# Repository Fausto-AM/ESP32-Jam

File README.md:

# ESP32-JAM

A high-performance 2.4 GHz signal jammer built on the **ESP32-WROOM** platform. It utilizes two independent **nRF24L01+PA+LNA** modules to sweep the 2.4 GHz spectrum in parallel, flooding the band with noise at maximum speed and power.

---

> [!WARNING]
> **DO NOT cross the USBs:** The ESP32 is powered directly via its `3V3` pin, bypassing its onboard regulator. **Never** connect a USB cable to the ESP32 dev board for programming while the device is powered by the battery or charging via the TP4056. It will cause a voltage conflict and permanently damage the ESP32 or the LDO. Turn the slide switch OFF before flashing.

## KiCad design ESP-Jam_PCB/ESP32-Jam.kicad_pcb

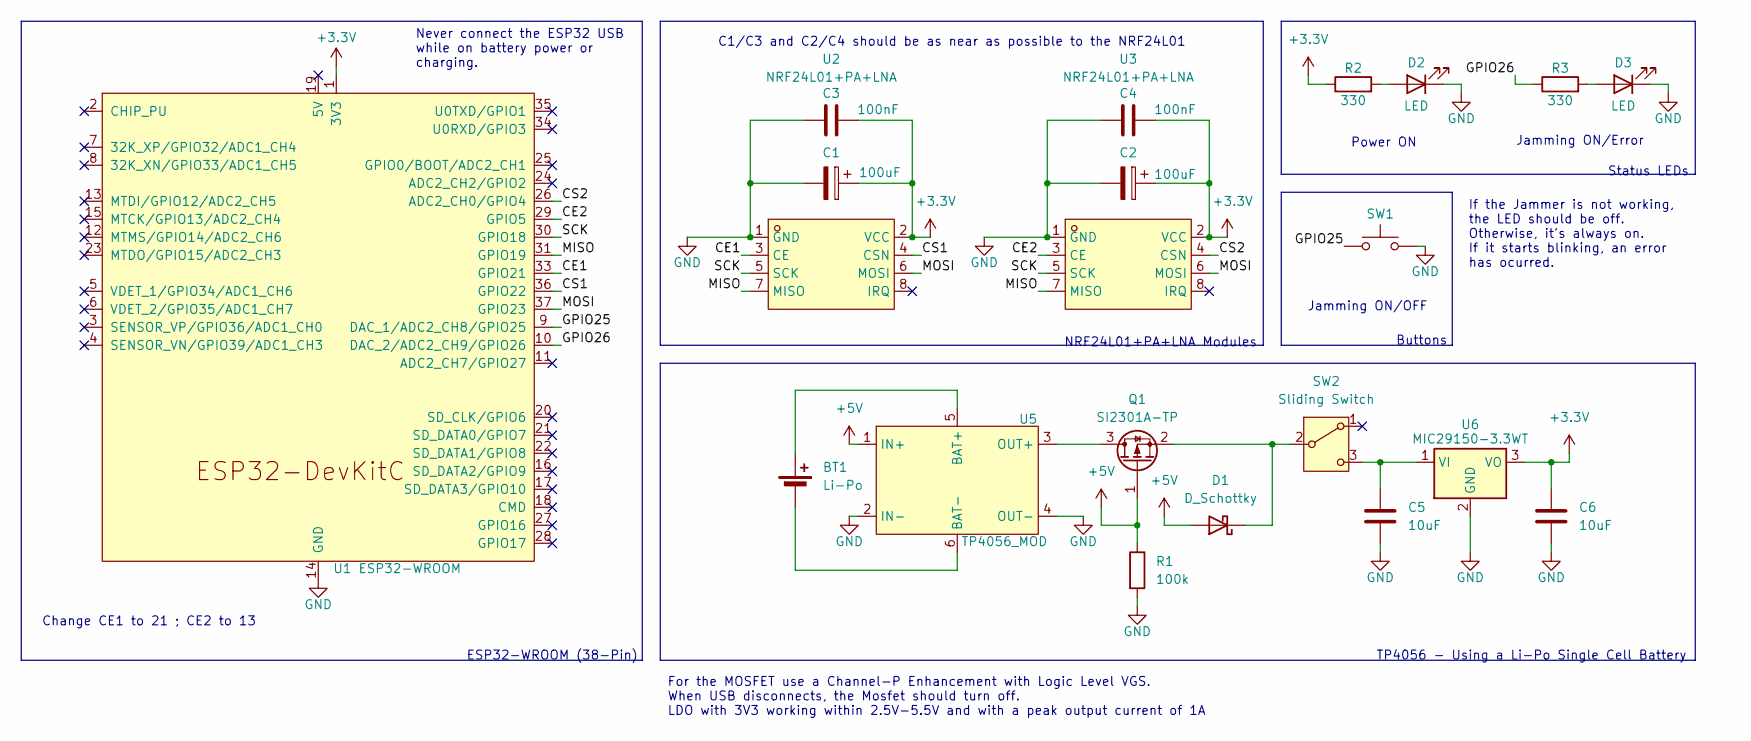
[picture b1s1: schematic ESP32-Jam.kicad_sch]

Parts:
BT1: Li-Po; JST_PH_B2B-PH-K_1x02_P2.00mm_Vertical
C1, C2: 100uF; CP_Radial_D5.0mm_P2.50mm
C3, C4: 100nF; C_Disc_D4.3mm_W1.9mm_P5.00mm
C5, C6: 10uF; C_Disc_D4.3mm_W1.9mm_P5.00mm
D1: D_Schottky; D_DO-35_SOD27_P10.16mm_Horizontal
D2, D3: LED; LED_D1.8mm_W3.3mm_H2.4mm
Q1: SI2301A-TP; SOT-23_Handsoldering
R1: 100k; R_Axial_DIN0204_L3.6mm_D1.6mm_P7.62mm_Horizontal
R2, R3: 330; R_Axial_DIN0204_L3.6mm_D1.6mm_P7.62mm_Horizontal
SW1: SW_Push; SW_TH_Tactile_Omron_B3F-102x
SW2: Sliding Switch; SW_Slide-03_Wuerth-WS-SLTV_10x2.5x6.4_P2.54mm
U1: ESP32-WROOM; ESP32-DevKitC
U2, U3: NRF24L01+PA+LNA; COMM-TH_L41.0-W15.5-P2.54_NRF24L01; MPN nRF24L01+PA+LNA; LCSC Part C9900187674
U5: TP4056_MOD; TP4056-Module
U6: MIC29150-3.3WT; TO-220-3_Horizontal_TabDown

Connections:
+3.3V: C1.1, C2.1, C3.2, C4.2, C6.1, R2.1, U1.1 (3V3), U2.2 (VCC), U3.2 (VCC), U6.3 (VO)
+5V: D1.2 (A), Q1.1 (G), R1.1, U5.1 (IN+)
/CE1: U1.33 (GPIO21), U2.3 (CE)
/CE2: U1.29 (GPIO5), U3.3 (CE)
/CS1: U1.36 (GPIO22), U2.4 (CSN)
/CS2: U1.26 (ADC2_CH0/GPIO4), U3.4 (CSN)
/GPIO25: SW1.1, U1.9 (DAC_1/ADC2_CH8/GPIO25)
/GPIO26: R3.1, U1.10 (DAC_2/ADC2_CH9/GPIO26)
/MISO: U1.31 (GPIO19), U2.7 (MISO), U3.7 (MISO)
/MOSI: U1.37 (GPIO23), U2.6 (MOSI), U3.6 (MOSI)
/SCK: U1.30 (GPIO18), U2.5 (SCK), U3.5 (SCK)
GND: C1.2, C2.2, C3.1, C4.1, C5.2, C6.2, D2.1 (K), D3.1 (K), R1.2, SW1.2, U1.14 (GND), U1.32 (GND), U1.38 (GND), U2.1 (GND), U3.1 (GND), U5.2 (IN-), U5.4 (OUT-), U6.2 (GND)
unnamed: BT1.1 (+), U5.5 (BAT+)
unnamed: BT1.2 (-), U5.6 (BAT-)
unnamed: D1.1 (K), Q1.2 (S), SW2.2 (B)
unnamed: D2.2 (A), R2.2
unnamed: D3.2 (A), R3.2
unnamed: Q1.3 (D), U5.3 (OUT+)
unnamed: C5.1, SW2.3 (C), U6.1 (VI)

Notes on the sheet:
Power ON
Buttons
Jamming ON/Error
Jamming ON/OFF
Change CE1 to 21 ; CE2 to 13
NRF24L01+PA+LNA Modules
Status LEDs
TP4056 - Using a Li-Po Single Cell Battery
C1/C3 and C2/C4 should be as near as possible to the NRF24L01
ESP32-WROOM (38-Pin)
For the MOSFET use a Channel-P Enhancement with Logic Level VGS. When USB disconnects, the Mosfet should turn off. LDO with 3V3 working within 2.5V-5.5V and with a peak output current of 1A
Never connect the ESP32 USB while on battery power or charging.
If the Jammer is not working, the LED should be off. Otherwise, it's always on. If it starts blinking, an error has ocurred.

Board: 2 copper layers, 21 parts (0 on the bottom side), 19 nets, no tracks yet.
